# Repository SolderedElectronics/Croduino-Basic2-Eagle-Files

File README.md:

# Croduino Basic2 Eagle Files
## Image

[Croduino Basic2(100025)](https://e-radionica.com/en/croduino-basic2.html)

## Description and details
Croduino Basic2 is 100% Arduino compatible board made in EU(Croatia), created to promote Arduino culture in Croatia(well, it's named CROduino). Install Arduino software, plug it into USB and start DIY-ing!

It has even more analog inputs than Arduino Uno, features Silabs USB to UART bridge and built-in voltage regulator. The main difference from original Arduino and Croduino is size. Croduino is just 5cm x 3cm which makes it very easy to implement into projects. More:

- Atmega328 microcontroller(32kB flash, 2kB RAM, 1kB EEPROM)
- Silabs CP2102 USB to UART bridge
- 22 I/O pins, 14 digital I/O, 6 PWM, 8 analog pins
- Size only 3 x 5cm (1.2 x 2 inch)
- LED light on the 13th pin
- Voltage regulator for possibility of external charging
- Protection fuse
- Breadboard friendly
- Made in Croatia
- Free lifetime technical support at techsupport@e-radionica.com

Microcontroller on-board is loaded with Arduino Optiboot bootloader.

## Repository content
This repo contains Cadsoft Eagle .sch and .brd files for Croduino Basic2 board. It also contains schematic in .pdf created from .sch Eagle file. 
Files have been arranged into folders for navigating between different versions of board. 
Tip: layer 200 shows top silkscreen and layer 208 should be bottom silkscreen. tParts and bParts layers are not used.

## Docs
- [Croduino Basic product page] (https://e-radionica.com/en/croduino-basic2.html)
- [Croduino lessons - on croatian language] (https://vimeo.com/channels/croduino)

## Board versions
- v0.9b - test version, same copper, different silkscreen
- v1.0 REV A - inital published version 

## License info
This product is open-source. Yay!
For any tech questions, contact us at techsupport@e-radionica.com
If you find an Issue, please open one at GitHub. If you can improve our product, fork us.

e-radionica.com Team.

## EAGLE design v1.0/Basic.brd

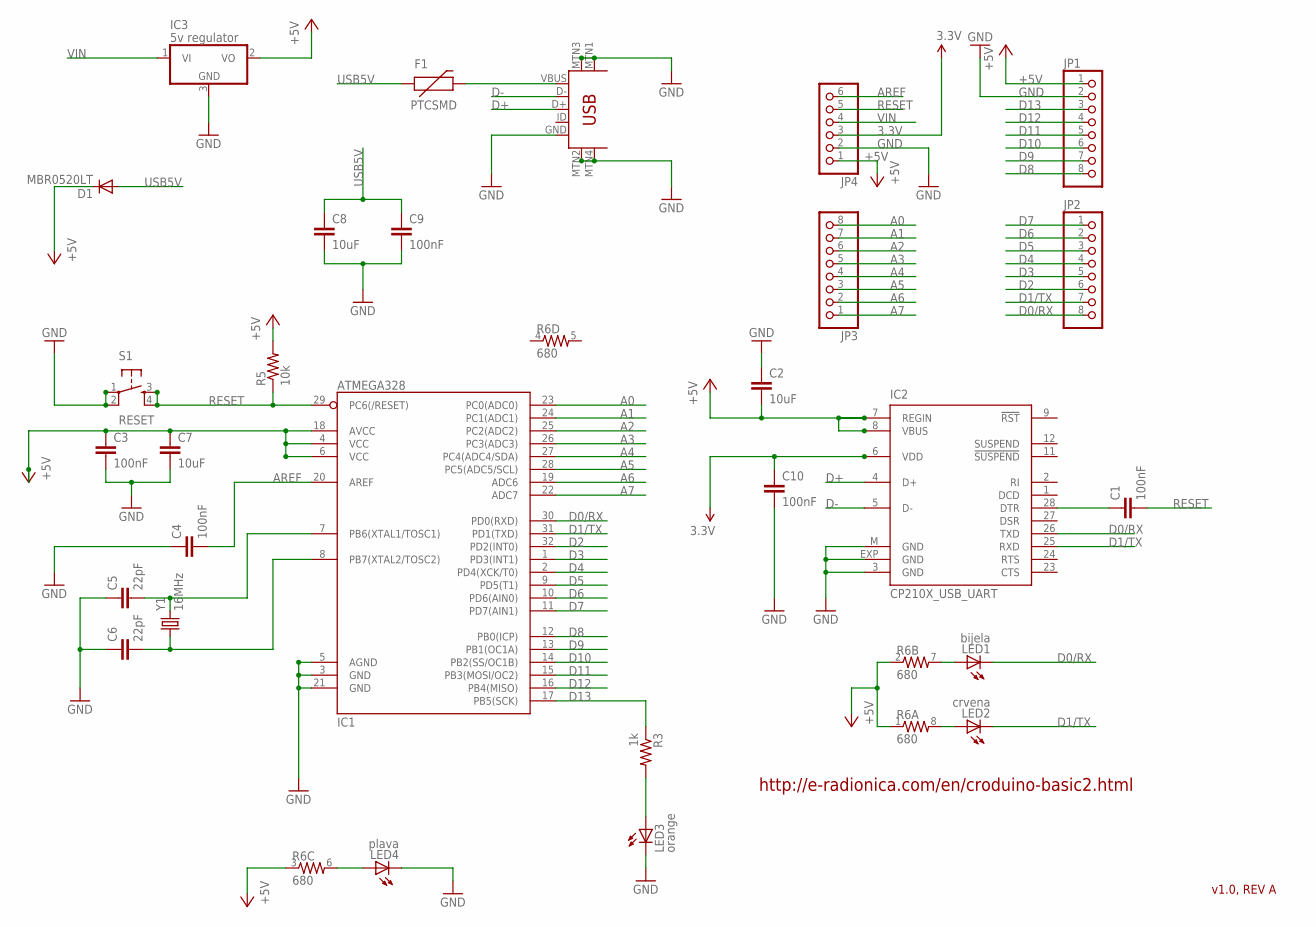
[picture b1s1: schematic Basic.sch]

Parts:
C1, C3, C4, C9, C10: 100nF; 0603-CAP
C2, C7, C8: 10uF; C3216
C5, C6: 22pF; 0603-CAP
D1: MBR0520LT; SOD123
F1: PTCSMD; PTC-1206
IC1: ATMEGA328; TQFP32-08
IC2: CP210X_USB_UART; MLP28
IC3: 5v regulator; TO252
JP1, JP2, JP3: PINHD-1X8BIG; 1X08-BIG
JP4: PINHD-1X6B; 1X06-BIG
LED1: bijela; CHIP-LED0805
LED2: crvena; CHIP-LED0805
LED3: orange; CHIP-LED0805
LED4: plava; CHIP-LED0805
R3: 1k; 0603-RES
R5: 10k; 0603-RES
R6: 680; 0603-ARV
S1: RESET; TACTILE_SWITCH_SMD
U1: USB-MINIB
Y1: 16MHz; CRYSTAL-SMD-5X3

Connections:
3.3V: C10.1, IC2.6 (VDD), JP4.3
+5V: C2.2, C3.1, C7.1, D1.C, IC1.4 (VCC), IC1.6 (VCC), IC1.18 (AVCC), IC2.7 (REGIN), IC2.8 (VBUS), IC3.2 (VO), JP1.1, JP4.1, R5.2, R6.1, R6.2 (1), R6.3 (1)
A0: IC1.23 (PC0(ADC0)), JP3.8
A1: IC1.24 (PC1(ADC1)), JP3.7
A2: IC1.25 (PC2(ADC2)), JP3.6
A3: IC1.26 (PC3(ADC3)), JP3.5
A4: IC1.27 (PC4(ADC4/SDA)), JP3.4
A5: IC1.28 (PC5(ADC5/SCL)), JP3.3
A6: IC1.19 (ADC6), JP3.2
A7: IC1.22 (ADC7), JP3.1
AREF: C4.2, IC1.20 (AREF), JP4.6
CRYSTAL1: C5.2, IC1.7 (PB6(XTAL1/TOSC1)), Y1.3 (2)
CRYSTAL2: C6.2, IC1.8 (PB7(XTAL2/TOSC2)), Y1.1
D0/RX: IC1.30 (PD0(RXD)), IC2.26 (TXD), JP2.8, LED1.C
D1/TX: IC1.31 (PD1(TXD)), IC2.25 (RXD), JP2.7, LED2.C
D2: IC1.32 (PD2(INT0)), JP2.6
D3: IC1.1 (PD3(INT1)), JP2.5
D4: IC1.2 (PD4(XCK/T0)), JP2.4
D5: IC1.9 (PD5(T1)), JP2.3
D6: IC1.10 (PD6(AIN0)), JP2.2
D7: IC1.11 (PD7(AIN1)), JP2.1
D8: IC1.12 (PB0(ICP)), JP1.8
D9: IC1.13 (PB1(OC1A)), JP1.7
D10: IC1.14 (PB2(SS/OC1B)), JP1.6
D11: IC1.15 (PB3(MOSI/OC2)), JP1.5
D12: IC1.16 (PB4(MISO)), JP1.4
D13: IC1.17 (PB5(SCK)), JP1.3, R3.1
D+: IC2.4 (D+), U1.D+
D-: IC2.5 (D-), U1.D-
GND: C2.1, C3.2, C4.1, C5.1, C6.1, C7.2, C8.2, C9.2, C10.2, IC1.3 (GND), IC1.5 (AGND), IC1.21 (GND), IC2.3 (GND), IC2.EXP (GND), IC2.M (GND), IC3.3 (GND), JP1.2, JP4.2, LED3.C, LED4.C, S1.1, S1.2, U1.GND, U1.MTN1 (MTN2), U1.MTN2 (MTN3), U1.MTN3 (MTN1), U1.MTN4
unnamed: LED1.A, R6.7 (2)
unnamed: LED2.A, R6.8 (2)
unnamed: F1.2, U1.VBUS
NAR_LED: LED3.A, R3.2
PLV_LED: LED4.A, R6.6 (2)
RESET: C1.2, IC1.29 (PC6(/RESET)), JP4.5, R5.1, S1.3, S1.4
RST_PRIJE_KOND: C1.1, IC2.28 (DTR)
USB5V: C8.1, C9.1, D1.A, F1.1
VIN: IC3.1 (VI), JP4.4

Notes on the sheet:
v1.0, REV A
http://e-radionica.com/en/croduino-basic2.html

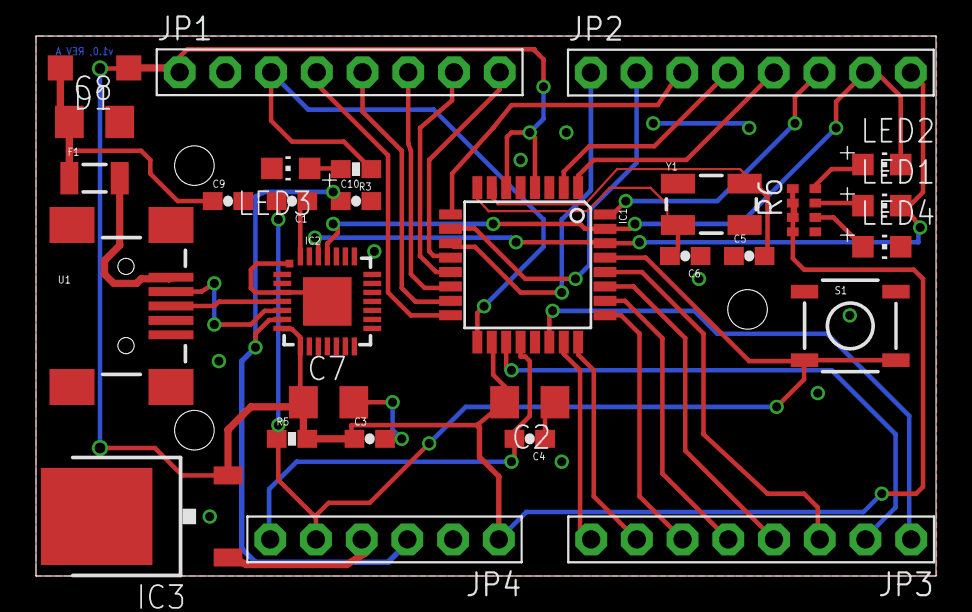
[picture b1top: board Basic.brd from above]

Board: 2 copper layers, 50.0 x 30.0 mm, 38 parts (0 on the bottom side), 39 nets.

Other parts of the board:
U$1: BASIC2_LED
U$2: BASIC2_ANALOG
U$3: BASIC2_ANALOG2
U$4: BASIC2_DIGITAL
U$5: BASIC2_DIGITAL2
U$6, U$7: NOVI_LOGO-4MM
U$8: CRODUINO_BASIC2
U$9: BASIC2_BOTTOM

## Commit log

2015-10-11 Inital upload of Eagle files and README
2015-11-03 README typo
2016-02-12 README change
    Changed links on e-radionica.com from HTTP to HTTPS since we enabled
    SSL.
2018-11-26 README update

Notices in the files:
parts and their libraries:
SparkFun: Licensing: CC v3.0 Share-Alike You are welcome to use this library for commercial purposes.
SparkFun-DigitalIC: Licensing: Creative Commons ShareAlike 4.0 International - https://creativecommons.org/licenses/by-sa/4.0
